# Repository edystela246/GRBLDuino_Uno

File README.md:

# GRBLDuino_Uno
Arduino Uno with integrated GRBL v1.1 CNC controller (GBRLDuino Uno)

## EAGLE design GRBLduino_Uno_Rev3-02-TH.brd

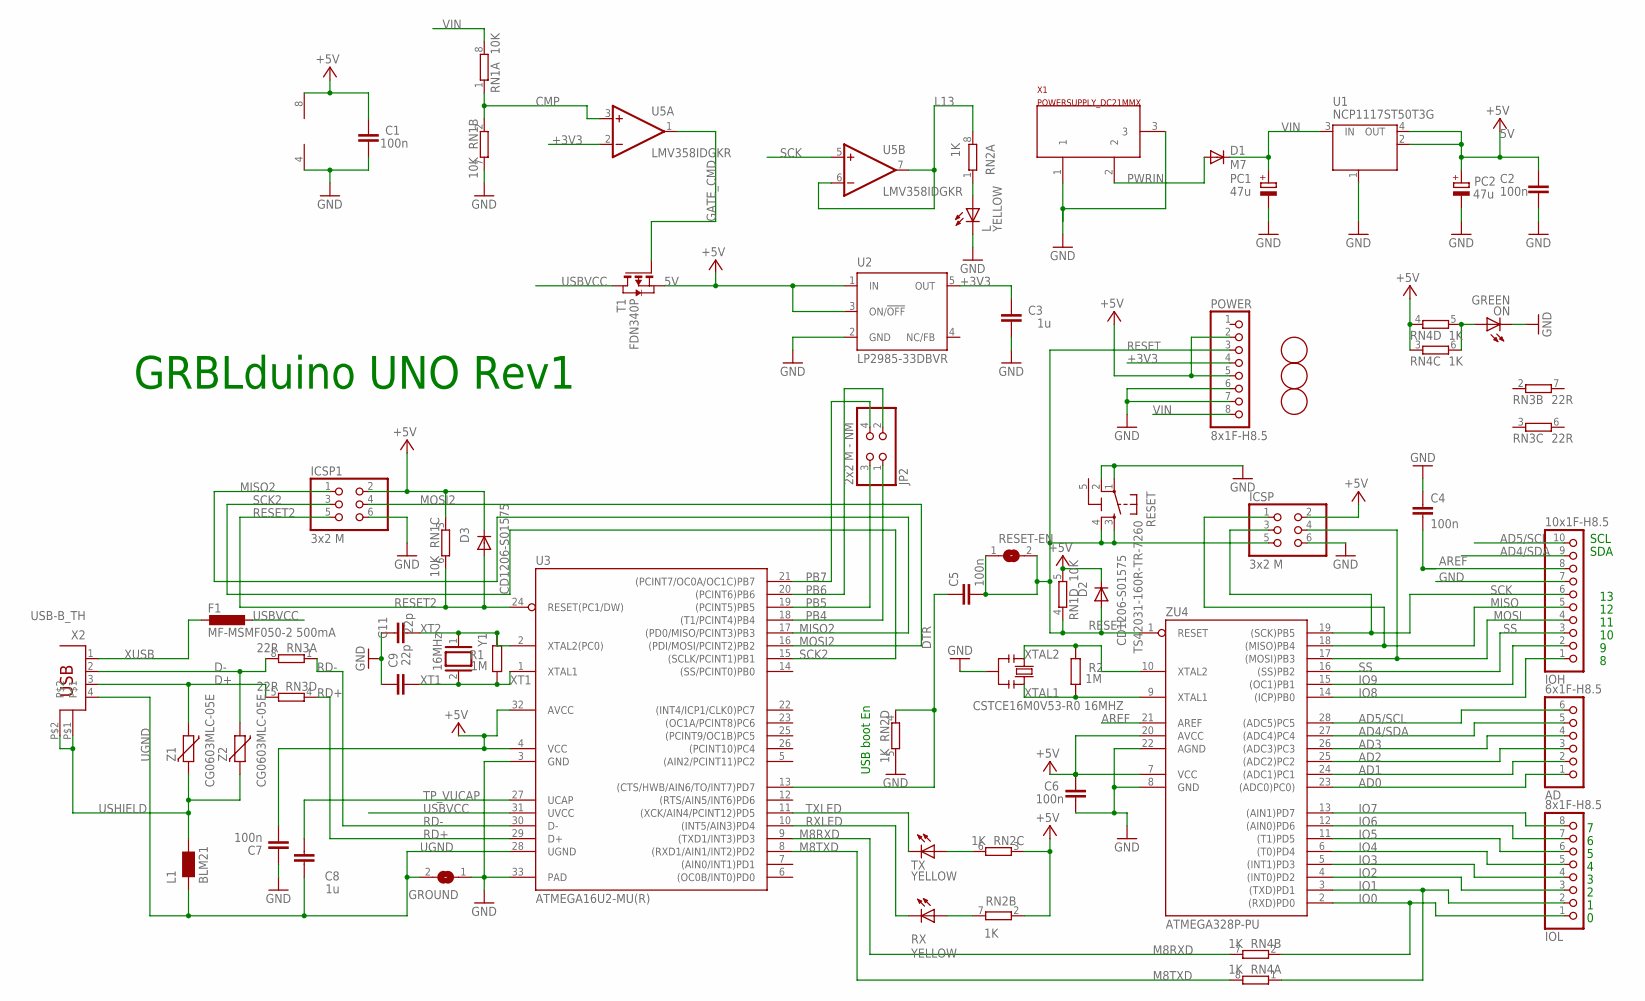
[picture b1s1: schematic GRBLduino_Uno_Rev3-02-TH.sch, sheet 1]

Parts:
AD: 6x1F-H8.5; 1X06
C1, C2, C4, C5, C6, C7: 100n; C0603-ROUND
C3, C8: 1u; C0603-ROUND
C9, C11: 22p; C0603-ROUND
D1: M7; SMB
D2, D3: CD1206-S01575; MINIMELF
F1: MF-MSMF050-2 500mA; L1812
FD1, FD2, FD3: FIDUCIALMOUNT; FIDUCIA-MOUNT
GROUND: SJ
ICSP, ICSP1: 3x2 M; 2X03
IOH: 10x1F-H8.5; 1X10
IOL: 8x1F-H8.5; 1X08
JP2: 2x2 M - NM; 2X02
L: YELLOW; CHIP-LED0805
L1: BLM21; 0805
ON: GREEN; CHIP-LED0805
PC1, PC2: 47u; PANASONIC_D
POWER: 8x1F-H8.5; 1X08
R1, R2: 1M; R0603-ROUND
RESET: TS42031-160R-TR-7260; TS42
RESET-EN: SJ
RN1: 10K; CAY16
RN2, RN4: 1K; CAY16
RN3: 22R; CAY16
RX: YELLOW; CHIP-LED0805
T1: FDN340P; SOT-23
TX: YELLOW; CHIP-LED0805
U1: NCP1117ST50T3G; SOT223
U2: LP2985-33DBVR; SOT23-DBV
U3: ATMEGA16U2-MU(R); MLF32
U5: LMV358IDGKR; MSOP08
X1: POWERSUPPLY_DC21MMX; POWERSUPPLY_DC-21MM
X2: USB-B_TH; PN61729
Y1: 16MHz; QS
Y2: CSTCE16M0V53-R0 16MHZ; RESONATOR
Z1, Z2: CG0603MLC-05E; CT/CN0603
ZU4: ATMEGA328P-PU; DIL28-3

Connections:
5-GND: RESET.5 (5-GND)
5V: C1.2, C2.2, C6.2, C7.1, D2.C, D3.C, ICSP.2, ICSP1.2, PC2.+, POWER.2, POWER.5, RN1.3 (1), RN1.5 (2), RN2.2 (1), RN2.3 (1), RN4.3 (1), RN4.4 (1), T1.2 (S), U1.2 (OUT), U1.4 (OUT), U2.1 (IN), U2.3 (ON/!OFF), U3.4 (VCC), U3.32 (AVCC), U5.8 (V+), ZU4.7 (VCC), ZU4.20 (AVCC); also elsewhere on the board
+3V3: C3.2, POWER.4, U2.5 (OUT), U5.2 (-IN)
AD0: AD.1, ZU4.23 ((ADC0)PC0)); also elsewhere on the board
AD1: AD.2, ZU4.24 ((ADC1)PC1); also elsewhere on the board
AD2: AD.3, ZU4.25 ((ADC2)PC2); also elsewhere on the board
AD3: AD.4, ZU4.26 ((ADC3)PC3); also elsewhere on the board
AD4/SDA: AD.5, IOH.9, ZU4.27 ((ADC4)PC4); also elsewhere on the board
AD5/SCL: AD.6, IOH.10, ZU4.28 ((ADC5)PC5); also elsewhere on the board
AREF: C4.2, IOH.8, ZU4.21 (AREF)
CMP: RN1.1, RN1.2 (1), U5.3 (+IN)
D+: RN3.5 (2), X2.3, Z1.1
D-: RN3.8 (2), X2.2, Z2.1
DTR: C5.1, RN2.4 (1), U3.13 ((CTS/HWB/AIN6/TO/INT7)PD7)
GATE_CMD: T1.3 (G), U5.1 (OUT)
GND: C1.1, C2.1, C3.1, C4.1, C6.1, C7.2, C9.2, C11.2, GROUND.1, ICSP.6, ICSP1.6, IOH.7, L.C, ON.C, PC1.-, PC2.-, POWER.6, POWER.7, RESET.1, RESET.2, RN1.7 (2), RN2.5 (2), U1.1 (GND/ADJ), U2.2 (GND), U3.3 (GND), U3.33 (PAD), U5.4 (V-), X1.1, X1.3, Y2.2, ZU4.8 (GND), ZU4.22 (AGND); also elsewhere on the board
IO0: IOL.1, RN4.2 (1), ZU4.2 ((RXD)PD0)
IO1: IOL.2, RN4.1, ZU4.3 ((TXD)PD1)
IO2: IOL.3, ZU4.4 ((INT0)PD2); also elsewhere on the board
IO3: IOL.4, ZU4.5 ((INT1)PD3); also elsewhere on the board
IO4: IOL.5, ZU4.6 ((T0)PD4); also elsewhere on the board
IO5: IOL.6, ZU4.11 ((T1)PD5); also elsewhere on the board
IO6: IOL.7, ZU4.12 ((AIN0)PD6); also elsewhere on the board
IO7: IOL.8, ZU4.13 ((AIN1)PD7); also elsewhere on the board
IO8: IOH.1, ZU4.14 ((ICP)PB0); also elsewhere on the board
IO9: IOH.2, ZU4.15 ((OC1)PB1); also elsewhere on the board
L13: RN2.8 (2), U5.6 (-IN), U5.7 (OUT)
M8RXD: RN4.7 (2), U3.9 ((TXD1/INT3)PD3)
M8TXD: RN4.8 (2), U3.8 ((RXD1/AIN1/INT2)PD2)
MISO: ICSP.1, IOH.5, ZU4.18 ((MISO)PB4); also elsewhere on the board
MISO2: ICSP1.1, U3.17 ((PD0/MISO/PCINT3)PB3)
MOSI: ICSP.4, IOH.4, ZU4.17 ((MOSI)PB3); also elsewhere on the board
MOSI2: ICSP1.4, U3.16 ((PDI/MOSI/PCINT2)PB2)
unnamed: L.A, RN2.1
unnamed: ON.A, RN4.5 (2), RN4.6 (2)
unnamed: RN2.7 (2), RX.A
unnamed: RN2.6 (2), TX.A
PB4: JP2.1, U3.18 ((T1/PCINT4)PB4)
PB5: JP2.3, U3.19 ((PCINT5)PB5)
PB6: JP2.2, U3.20 ((PCINT6)PB6)
PB7: JP2.4, U3.21 ((PCINT7/OC0A/OC1C)PB7)
PWRIN: D1.A, X1.2
RD+: RN3.4 (1), U3.29 (D+)
RD-: RN3.1, U3.30 (D-)
RESET: C5.2, D2.A, ICSP.5, POWER.3, RESET.3, RESET.4, RESET-EN.1, RESET-EN.2, RN1.4 (1), ZU4.1 (RESET); also elsewhere on the board
RESET2: D3.A, ICSP1.5, RN1.6 (2), U3.24 (RESET(PC1/DW))
RXLED: RX.C, U3.10 ((INT5/AIN3)PD4)
SCK: ICSP.3, IOH.6, U5.5 (+IN), ZU4.19 ((SCK)PB5); also elsewhere on the board
SCK2: ICSP1.3, U3.15 ((SCLK/PCINT1)PB1)
SS: IOH.3, ZU4.16 ((SS)PB2); also elsewhere on the board
TP_VUCAP: C8.1, U3.27 (UCAP)
TXLED: TX.C, U3.11 ((XCK/AIN4/PCINT12)PD5)
UGND: C8.2, GROUND.2, L1.1, U3.28 (UGND), X2.4
USBVCC: F1.1, T1.1 (D), U3.31 (UVCC)
USHIELD: L1.2, X2.P$1, X2.P$2, Z1.2, Z2.2
VIN: D1.C, PC1.+, POWER.8, RN1.8 (2), U1.3 (IN)
XT1: C9.1, R1.1, U3.1 (XTAL1), Y1.2
XT2: C11.1, R1.2, U3.2 (XTAL2(PC0)), Y1.1
XTAL1: R2.1, Y2.3, ZU4.9 (XTAL1)
XTAL2: R2.2, Y2.1, ZU4.10 (XTAL2)
XUSB: F1.2, X2.1

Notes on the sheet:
GRBLduino UNO Rev1
USB boot En
SDA
SCL

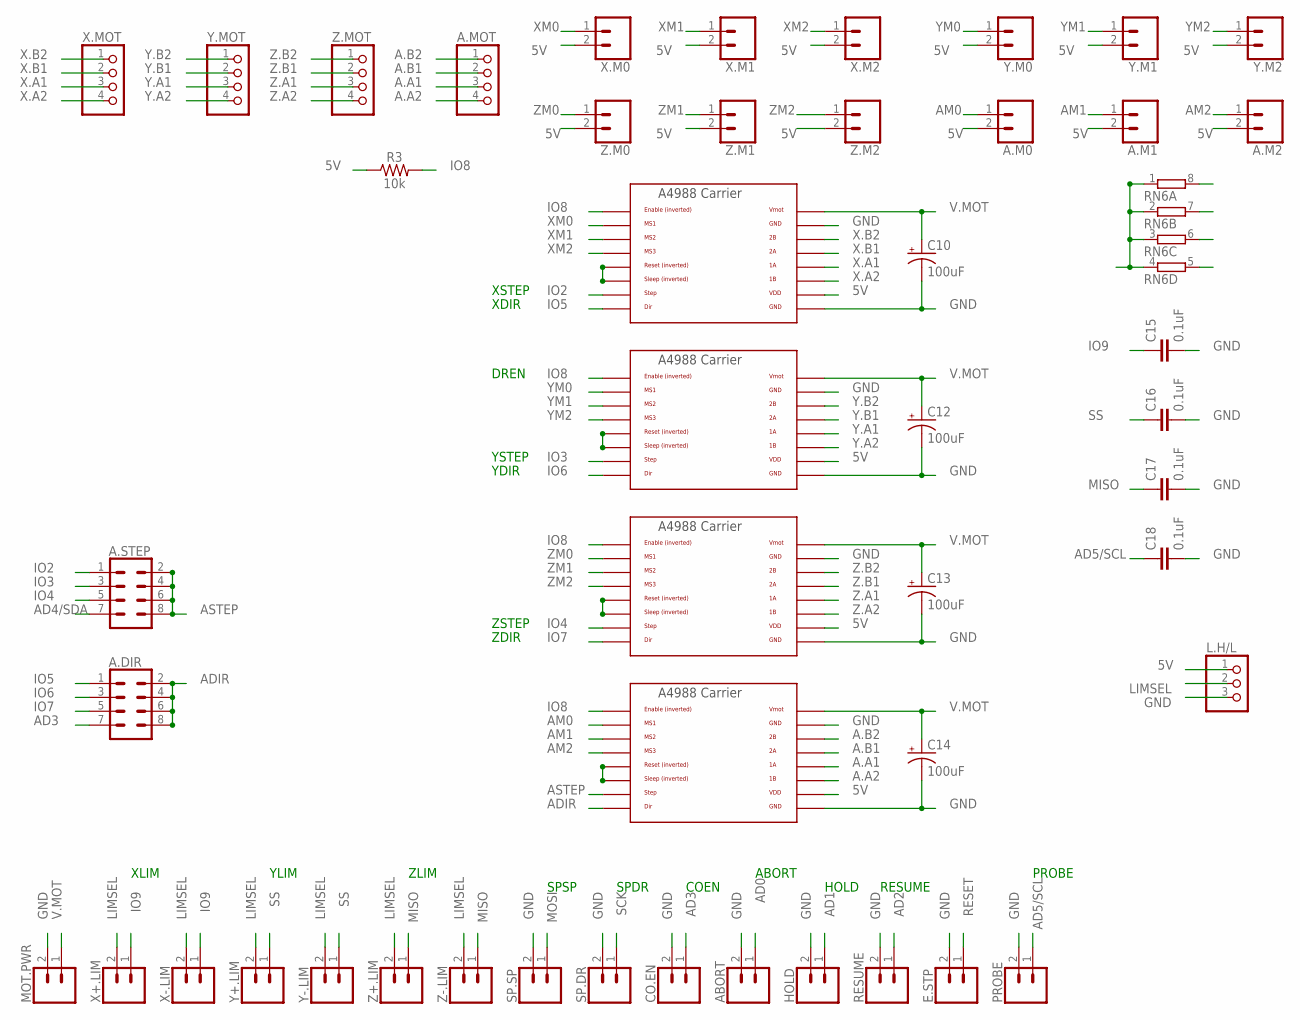
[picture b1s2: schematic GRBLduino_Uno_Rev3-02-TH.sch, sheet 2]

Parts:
A.DIR, A.STEP: CONN_04X2; 2X4
A.DRV: A Driver; A4988BREAKOUT
A.M0, A.M1, A.M2: CONN_02; 1X02
A.MOT: PINHD-1X4; 1X04
ABORT: CONN_025MM; SCREWTERMINAL-5MM-2
C10, C12, C13, C14: 100uF; CPOL-RADIAL-2.5MM-6.5MM
C15, C16, C17, C18: 0.1uF; 0603
CO.EN: CONN_025MM; SCREWTERMINAL-5MM-2
E.STP: CONN_025MM; SCREWTERMINAL-5MM-2
HOLD: CONN_025MM; SCREWTERMINAL-5MM-2
L.H/L: PINHD-1X3; 1X03
MOT.PWR: CONN_025MM; SCREWTERMINAL-5MM-2
PROBE: CONN_025MM; SCREWTERMINAL-5MM-2
R3: 10k; 0603
RESUME: CONN_025MM; SCREWTERMINAL-5MM-2
RN6: 4R-N0603-ARC; 0603-ARC
SP.DR, SP.SP: CONN_025MM; SCREWTERMINAL-5MM-2
X+.LIM: CONN_025MM; SCREWTERMINAL-5MM-2
X-.LIM: CONN_025MM; SCREWTERMINAL-5MM-2
X.DRV: X Driver; A4988BREAKOUT
X.M0, X.M1, X.M2: CONN_02; 1X02
X.MOT: PINHD-1X4; 1X04
Y+.LIM: CONN_025MM; SCREWTERMINAL-5MM-2
Y-.LIM: CONN_025MM; SCREWTERMINAL-5MM-2
Y.DRV: Y Driver; A4988BREAKOUT
Y.M0, Y.M1, Y.M2: CONN_02; 1X02
Y.MOT: PINHD-1X4; 1X04
Z+.LIM: CONN_025MM; SCREWTERMINAL-5MM-2
Z-.LIM: CONN_025MM; SCREWTERMINAL-5MM-2
Z.DRV: Z Driver; A4988BREAKOUT
Z.M0, Z.M1, Z.M2: CONN_02; 1X02
Z.MOT: PINHD-1X4; 1X04

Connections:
5V: A.DRV.VDD, A.M0.2, A.M1.2, A.M2.2, L.H/L.1, R3.1, RN6.1, RN6.2 (1), RN6.3 (1), RN6.4 (1), X.DRV.VDD, X.M0.2, X.M1.2, X.M2.2, Y.DRV.VDD, Y.M0.2, Y.M1.2, Y.M2.2, Z.DRV.VDD, Z.M0.2, Z.M1.2, Z.M2.2; also elsewhere on the board
A.A1: A.DRV.1A, A.MOT.3
A.A2: A.DRV.1B, A.MOT.4
A.B1: A.DRV.2A, A.MOT.2
A.B2: A.DRV.2B, A.MOT.1
AD0: ABORT.1; also elsewhere on the board
AD1: HOLD.1; also elsewhere on the board
AD2: RESUME.1; also elsewhere on the board
AD3: A.DIR.7, CO.EN.1; also elsewhere on the board
AD4/SDA: A.STEP.7; also elsewhere on the board
AD5/SCL: C18.1, PROBE.1, RN6.5 (2); also elsewhere on the board
ADIR: A.DIR.2, A.DIR.4, A.DIR.6, A.DIR.8, A.DRV.DIR
AM0: A.DRV.MS1, A.M0.1
AM1: A.DRV.MS2, A.M1.1
AM2: A.DRV.MS3, A.M2.1
ASTEP: A.DRV.STEP, A.STEP.2, A.STEP.4, A.STEP.6, A.STEP.8
GND: A.DRV.GND, A.DRV.GND@0 (GND), ABORT.2, C10.2 (-), C12.2 (-), C13.2 (-), C14.2 (-), C15.2, C16.2, C17.2, C18.2, CO.EN.2, E.STP.2, HOLD.2, L.H/L.3, MOT.PWR.2, PROBE.2, RESUME.2, SP.DR.2, SP.SP.2, X.DRV.GND, X.DRV.GND@0 (GND), Y.DRV.GND, Y.DRV.GND@0 (GND), Z.DRV.GND, Z.DRV.GND@0 (GND); also elsewhere on the board
IO2: A.STEP.1, X.DRV.STEP; also elsewhere on the board
IO3: A.STEP.3, Y.DRV.STEP; also elsewhere on the board
IO4: A.STEP.5, Z.DRV.STEP; also elsewhere on the board
IO5: A.DIR.1, X.DRV.DIR; also elsewhere on the board
IO6: A.DIR.3, Y.DRV.DIR; also elsewhere on the board
IO7: A.DIR.5, Z.DRV.DIR; also elsewhere on the board
IO8: A.DRV.EN, R3.2, X.DRV.EN, Y.DRV.EN, Z.DRV.EN; also elsewhere on the board
IO9: C15.1, RN6.8 (2), X+.LIM.1, X-.LIM.1; also elsewhere on the board
LIMSEL: L.H/L.2, X+.LIM.2, X-.LIM.2, Y+.LIM.2, Y-.LIM.2, Z+.LIM.2, Z-.LIM.2
MISO: C17.1, RN6.6 (2), Z+.LIM.1, Z-.LIM.1; also elsewhere on the board
MOSI: SP.SP.1; also elsewhere on the board
unnamed: X.DRV.RST, X.DRV.SLP (SLEEP)
unnamed: Y.DRV.RST, Y.DRV.SLP (SLEEP)
unnamed: Z.DRV.RST, Z.DRV.SLP (SLEEP)
unnamed: A.DRV.RST, A.DRV.SLP (SLEEP)
RESET: E.STP.1; also elsewhere on the board
SCK: SP.DR.1; also elsewhere on the board
SS: C16.1, RN6.7 (2), Y+.LIM.1, Y-.LIM.1; also elsewhere on the board
V.MOT: A.DRV.VMOT, C10.1 (+), C12.1 (+), C13.1 (+), C14.1 (+), MOT.PWR.1, X.DRV.VMOT, Y.DRV.VMOT, Z.DRV.VMOT
X.A1: X.DRV.1A, X.MOT.3
X.A2: X.DRV.1B, X.MOT.4
X.B1: X.DRV.2A, X.MOT.2
X.B2: X.DRV.2B, X.MOT.1
XM0: X.DRV.MS1, X.M0.1
XM1: X.DRV.MS2, X.M1.1
XM2: X.DRV.MS3, X.M2.1
Y.A1: Y.DRV.1A, Y.MOT.3
Y.A2: Y.DRV.1B, Y.MOT.4
Y.B1: Y.DRV.2A, Y.MOT.2
Y.B2: Y.DRV.2B, Y.MOT.1
YM0: Y.DRV.MS1, Y.M0.1
YM1: Y.DRV.MS2, Y.M1.1
YM2: Y.DRV.MS3, Y.M2.1
Z.A1: Z.DRV.1A, Z.MOT.3
Z.A2: Z.DRV.1B, Z.MOT.4
Z.B1: Z.DRV.2A, Z.MOT.2
Z.B2: Z.DRV.2B, Z.MOT.1
ZM0: Z.DRV.MS1, Z.M0.1
ZM1: Z.DRV.MS2, Z.M1.1
ZM2: Z.DRV.MS3, Z.M2.1

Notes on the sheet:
PROBE
COEN
RESUME
HOLD
ABORT
XSTEP
YSTEP
ZSTEP
XDIR
YDIR
ZDIR
DREN
XLIM
YLIM
SPSP
ZLIM
SPDR

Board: 2 copper layers, 100 parts (1 on the bottom side), 96 nets, no tracks yet.

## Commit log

2018-01-01 Initial upload

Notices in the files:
parts and their libraries:
SparkFun-Capacitors: Licensing: Creative Commons ShareAlike 4.0 International - https://creativecommons.org/licenses/by-sa/4.0
